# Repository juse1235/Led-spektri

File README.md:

# Led-spektri

Tuntuiko normaali haalarisalama liian yksinkertaiselta? Epäiletkö, että juotettavia LEDejä ei voi olla liikaa? Oletko aina haaveillut haalarimerkistä, jonka nähtyään kanssaopiskelijat pyörtyvät ihastuksesta?

Mikäli näin on, olet selvästikin motivoitunut nousemaan seuraavalle tasolle yöllisessä yökerhojen ja pystärien bling-bling-loisteessa. Tämä tanssilattioiden katseenvangitsija tarjoaa ainutkertaisen mahdollisuuden turruttaa itsensä vinoon juottuneille komponenteille ja v*tutukselle. Älä missaa tilaisuutta! Minä en missaisi.

Komponentit

| Tyyppi          |	Määrä  |	Huom                                                    |
| --------------- | ------ | -------------------------------------------------------- |
| Atmega328PB-AU  |1       |	Myös 328P voi toimia, mutta vaatii muutoksia kääntäjään |
| LED, 3 mm, jalallinen	|64 |	Ei värikoodia – käytä mielikuvitusta |
| Transistori, SOT-23|16 |	Käytössä MMBT4401, ei suurempaa väliä mallista, hyvä kuitenkin kestää vähintään 20 mA virtaa |
| Vastus, 0603 – 0805, 1+ kOhm | 16 |		Transistorien ohjaus |
| Etuvastus, 0805	|8	| Kirkkauden säätö, 100 – 500 ohmia lienee hyvä, säätää myös virrankulutusta, tekijällä käytössä 300 ohmia |
| Isohko vastus, noin 5 kOhm, 0603 |2	 | |
| Regulaattori, LP2985 – 3.3 |	1	| |
| Kondensaattori, 100 nF, 0805|	1	| |
| Kondensaattori, 10 uF, 0805|	1	| |
| Sulake, 500 mA, 1206	|1	| |
| Oskillaattori, 16 MHz |	1 |	Käytössä CSTCE16M0V53-R0 |
| MAX4466-mikrofonimoduuli |	1 |	Mikrofoneja löytyy eri herkkyyksillä, voi olla tuurissaan, mikä on käyttökelpoinen. Electret sinisellä piirilevyllä on toiminut toistaiseksi.|

## Yleinen toimintaperiaate
Ledien toimintaperiaate on samankaltainen kuin haalarisalamassakin, eli ledejä vilkutetaan matriisissa sarakkeittain säätämällä, mikä sarake saa yhteyden maahan ja suljettua virtapiirin. 

Mikrofoni kuuntelee ääntä, ja mikrokontrolleri lukee siitä tulevaa analogista signaalia jatkuvalla syötöllä. Näytepätkän ollessa valmis mikrokontrolleri tekee siitä fft-muunnoksen, joka voidaan esittää ledeillä.

Tähän merkkiin ei otettu edes mahdollisuudeksi käyttää 9 voltin paristolla, vaan käyttöjännite otetaan aina 5 voltin jännitelähteestä (lue: USB-kaapelin kautta varavirtalähteestä).

## Tarkempi piirikaavion analyysi
Piirikaavion olisi voinut päivittää paljon helpommin luettavaksi ja oikeille arvoille, jos Kicad 5.0 ei olisi niin epäyhteensopiva Kicad 4 -versioiden kanssa. 

Käyttöjännite tulee mikrokontrollerille ja 3,3 voltin regulaattorille sulakkeen kautta. Sulakkeen tehtävänä on luonnollisesti edes hieman suojata komponentteja oikosuluilta sun muilta lapsuksilta. Tässä otettiin mallia Arduinosta. Regulaattorin tarkoituksena on vain ja ainoastaan tuottaa tasaista käyttöjännitettä mikrofonimoduulille ja asettaa analoginen referenssitaso mikrokontrollerille mikrofonimoduulin analogisen signaalin lukua varten. 10 mikrofaradin kondensaattori C1 tasoittaa käyttöjännitteen pahimmat häiriöt, ja kondensaattori C_small (oikea arvo 100 nF) tekee saman 3,3 voltin linjalle.

Toisin kuin haalarisalamassa, tässä projektissa tarvitaan transistoreita rajoittamaan mikrokontrollerin kuormaa. Riittävän kirkkauden takaamiseksi ledin virraksi on hyvä määritellä noin 15 mA. Transistoreiksi päätyivät MMBT3904-transistorit, jotka perustuvat NPN-teknologiaan. Lähtökohtaisesti MOSFET-transistorienkin pitäisi toimia ihan yhtä hyvin, kunhan paketointi on sama. Transistorit vaativat vastukset kantavirran rajoittamiseksi (1 kOhmin vastukset piirikaaviossa ja jäljempänä esitetyssä piirilevyssä). Todennäköisesti arvoltaan suuremmatkin vastukset toimisivat aivan yhtä hyvin. 

##### HUOM!Projektia kokeiltiin toteuttaa myös puolella transistorimäärällä, mutta mikrokontrolleri ei kyennyt antamaan riittävästi virtaa yhden sarakkeen ledeille yhtä aikaa. Tämän korjaaminen vaatii joko todella herkkiä ja kirkkaita ledejä ja/tai koodimuutoksia, jolloin ainoastaan yksi led olisi samaan yhtä aikaa päällä (nyt maksimissaan kahdeksan).

Oskillaattori on geneerinen 16 megahertsin malli sisäänrakennetulla kuormakapasitanssilla, jollaisia näkee muun muassa Arduino Nanossa. Myös 20 megahertsin kidettä voi käyttää, mutta se vaatii muutoksia koodiin ja Atmegan… ööö, fuse… sulake ei liene oikea termi. Joka tapauksessa ”fuse”:ille pitää löytää oikeat asetukset.

Yksinkertaisuuden vuoksi mikrofonin kanssa päädyttiin vahvistimen sisältävään valmiiseen moduuliin. Moduuli tuottaa analogista signaalia, joka välitetään Atmegan ADC-pinniin, ja josta Atmega ottaa näytepätkän.

Kuten tarkimmat jo saattavat huomata, tekijä ei osannut tekovaiheessa tehdä ihmisystävällisiä kytkentöjä.

## Piirilevy
Tilanpuute oli valtava ongelma varsinaisen piirilevyn suunnittelun kanssa. Tästä syystä kaikkia komponentteja ei voitu sijoittaa levyn takapuolelle helpon korjattavuuden takaamiseksi, vaan osa komponenteista ja mikrofonimoduuli oli juotettava etupuolelle.

Yleinen ohje juottamiseen: juota ensin yksi komponentin nurkka kiinni niin, että komponentin muutkin juotoskohdat ovat paikallaan ja komponentti on oikeassa asennossa. Tämän jälkeen voi helposti juottaa loput paikat.

Juottaminen on hyvä aloittaa mikrokontrollerista. Tekijä juotti piirin reippaalla juoksutteella ja reippaalla tinankäytöllä, jolloin myös kontrollerin jalat olivat juottuneet yhteen. Tämän jälkeen ylimääräinen tina oli helppoa imeä tinaimunauhalla.

Muiden pintaliitoskomponenttien juottamisessa ei ole varsinaisesti mitään mainittavaa. U2 alemmassa kuvassa on 3,3 voltin regulaattori.
Kun pintaliitoskomponentit on juotettu, J7 ja J6 on yhdistettävä hyppylangalla. Miksi näin? Tilanpuutteen takia maatasoa ei ole muuten yhdistetty kontrollerin yläpuolelle ollenkaan. Onneksi tämä on matalan taajuuden sovellutus, joten tämmöiset temput ovat sallittuja...

Etupuolella on mainittava ledien juottamisesta sen verran, että pitkä jalka (anodi) menee ympyrän muotoiseen juotospisteeseen, ja lyhyt jalka (katodi) menee neliön muotoiseen juotospisteeseen. Kokemuksen jykevällä rintaäänellä voi sanoa, että juottakaa ledit myös mieluummin etupuolelle kuin takapuolelle. Mikrofonimoduulin ja piirilevyn väliin on suositeltavaa laittaa jotakin eristettä oikosulun välttämiseksi. Tantaalikondensaattorin viivalla merkitty pääty menee aina positiiviseen jännitteeseen kaiken järjen vastaisesti (etupuolen 10 mikrofaradin konkka). 

Levyn takapuoli

Levyn etupuoli

## Ohjelmointi
Ohjelmointi tapahtuu ISP-väylän kautta. ArduinoISP on tässä suositeltava ohjelmoija. Piirilevylle jätettiin ohjelmointipaikat myös UART-ohjelmointia varten, mutta niitä ei tässä tapauksessa tarvita ollenkaan. Tulevaisuuden generaatioista ne voikin poistaa tilaa säästääkseen.

##### Komennot Windowsille:

avrdude -C "C:\Program Files (x86)\Arduino\hardware\tools\avr\etc\avrdude.conf" -c avrisp -p m328pb -B3 -P COM7 -b 19200 -U flash:w:merkki.hex

avrdude -C "C:\Program Files (x86)\Arduino\hardware\tools\avr\etc\avrdude.conf" -c avrisp -p m328pb -B3 -P COM7 -b 19200 -U lfuse:w:0xff:m -U hfuse:w:0xde:m efuse:w:0x05:m

Jos avrdude.exe:ä ei ole asetettu Windowsin ympäristömuuttujiin, on edellä mainitut komennot ajettava ”Arduino\hardware\tools\avr\bin”-kansiosta. Polut ja oikea sarjaportti pitää toki tarkistaa tapauskohtaisesti.

##### Testaamattomat komennot Linuxille ja Macille:

avrdude -c avrisp -p m328pb -B3 -P /dev/ttyUSB0 -b 19200 -U flash:w:merkki.hex

avrdude -c avrisp -p m328pb -B3 -P /dev/ttyUSB0 -b 19200 -U lfuse:w:0xff:m -U hfuse:w:0xde:m efuse:w:0x05:m

Atmel Studio 7:llä tehty koodi ei ole mitään kauneinta katseltavaa, mutta joka tapauksessa se toimii. ChaN AVR FFT -kirjasto on otettu lievästi editoituna AVRFreaks-foorumilta ( https://www.avrfreaks.net/forum/64-point-fft-elm-chan-library), ja kirjasto löytyy myös erilaisina variaatioina eri puolilta internetiä. Alun perin koodi on oletettavasti julkaistu Elm-chanin kotisivulla (http://elm-chan.org/works/akilcd/report_e.html)

## Fyysinen rakenne
Kuumaliimaa kannattaa hyödyntää ainakin varsinaisen mikrofonielementin ja mikrofonimoduulipiirilevyn liitoskohdassa, sillä isku taittaa mikrofonin helposti. Lisäksi käyttöjännitetuloon on hyvä tehdä liimalla vedonpoisto.
Haalarimerkkiin integroimiseen ei ole suoria ohjeita, mutta on suositeltavaa tehdä painettuun merkkiin valmiit reiät. Mielikuvituksen ja insinööritaitojen käyttö on aiheellista, sillä ledien asentaminen merkin läpi haalarisalaman mukaisesti ei ole huollettavuuden takia järkevää.

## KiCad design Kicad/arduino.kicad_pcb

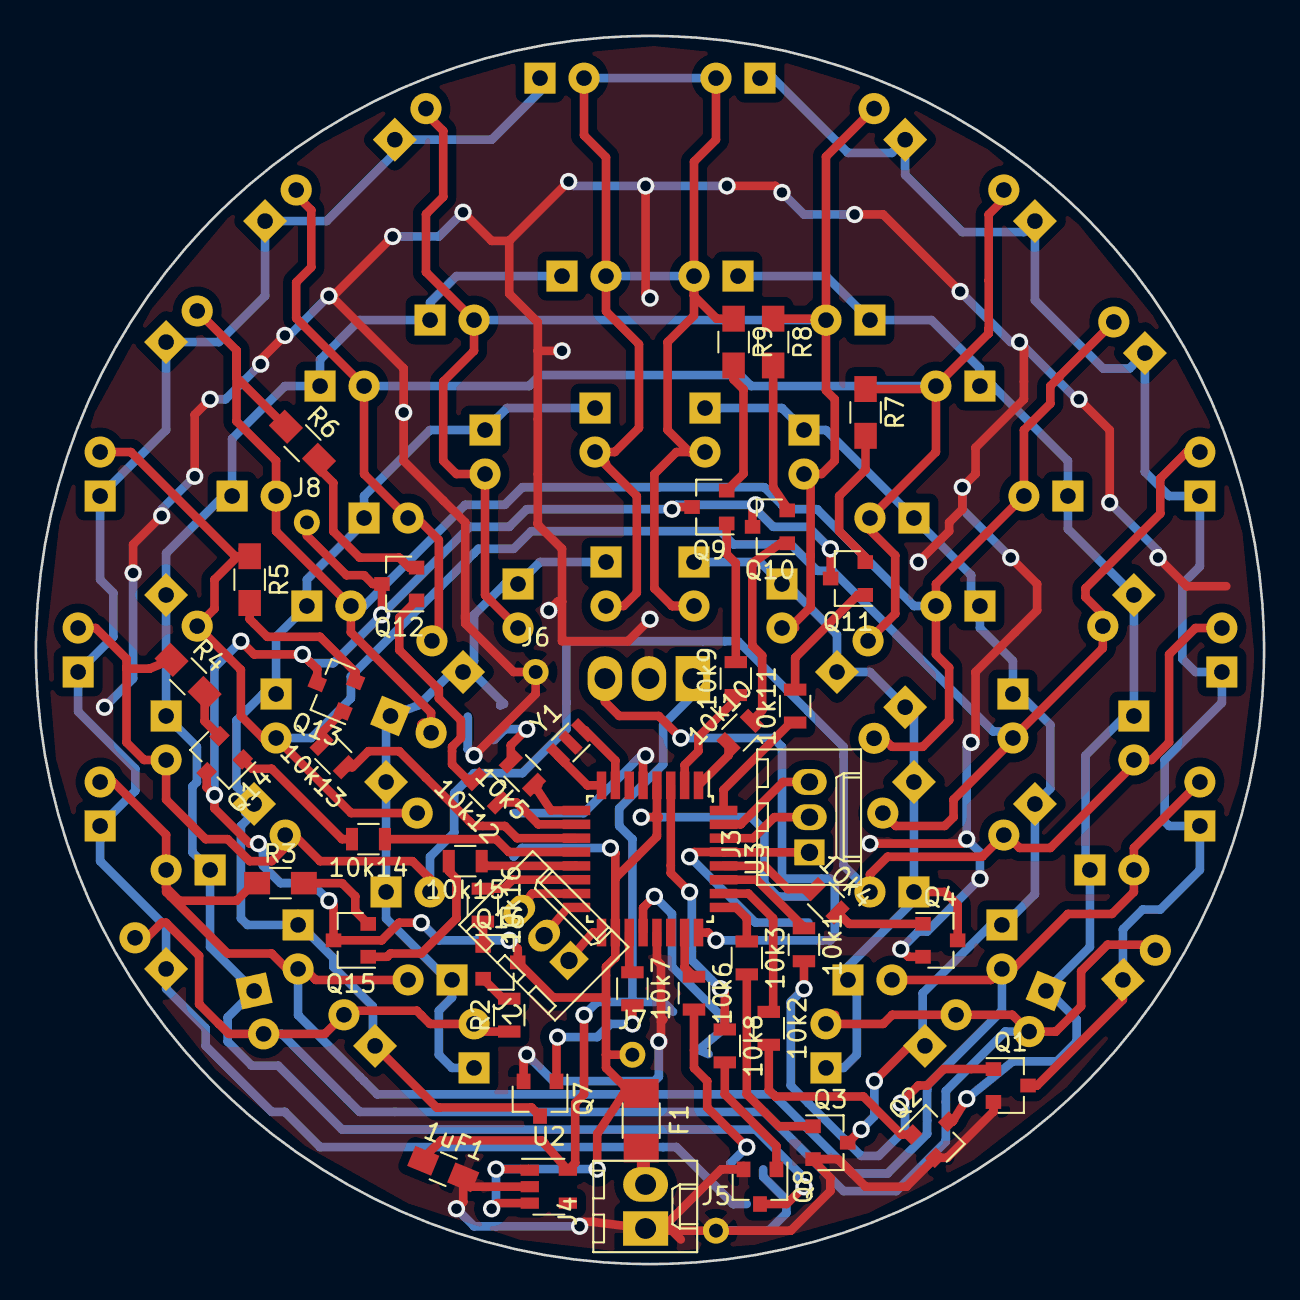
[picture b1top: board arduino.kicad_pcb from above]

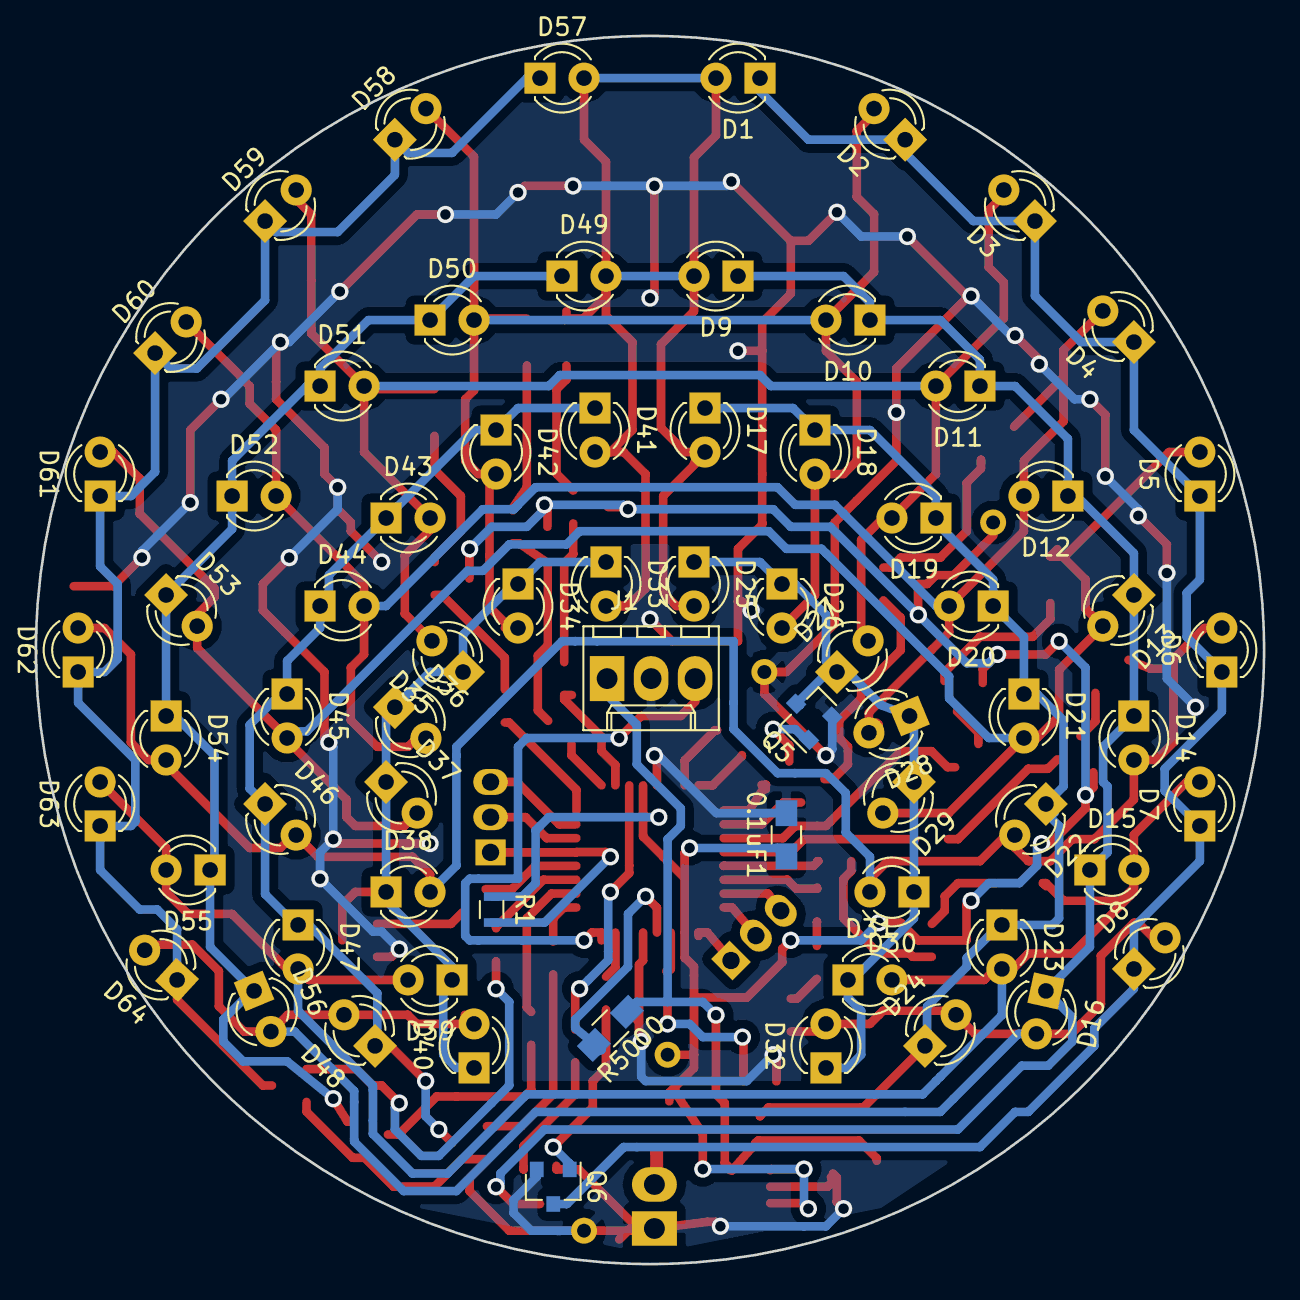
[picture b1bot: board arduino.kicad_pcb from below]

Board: 2 copper layers, 70.9 x 70.9 mm, 120 parts (70 on the bottom side), 70 nets.

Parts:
0.1uF1: C; C_0805_HandSoldering
1uF1: C_Small; C_0805_HandSoldering
10k1, 10k2, 10k3, 10k4, 10k5, 10k6, 10k7, 10k8, 10k9, 10k10, 10k11, 10k12, 10k13, 10k14, 10k15, 10k16: R; R_0805
D1, D2, D3, D4, D5, D6, D7, D8, D9, D10, D11, D12, D13, D14, D15, D16, D17, D18, D19, D20, D21, D22, D23, D24, D25, D26, D27, D28, D29, D30, D31, D32, D33, D34, D35, D36, D37, D38, D39, D40, D41, D42, D43, D44, D45, D46, D47, D48, D49, D50, D51, D52, D53, D54, D55, D56, D57, D58, D59, D60, D61, D62, D63, D64: IR204A; LED_D3.0mm
F1: 500mA; Fuse_SMD1206_Wave
J1: Conn_01x03; Molex_KK-6410-03_03x2.54mm_Straight
J2, J3: Conn_01x03; kolmijalka
J4: Conn_01x02; Molex_KK-6410-02_02x2.54mm_Straight
J5, J6, J7, J8: Conn_01x01; Measurement_Point_Round-TH_Small
Q1, Q2, Q3, Q4, Q5, Q6, Q7, Q8, Q9, Q10, Q11, Q12, Q13, Q14, Q15, Q16: MMBT3904; SOT-23
R1: 10kohm; L_0603
R2: R; R_0805
R3, R4, R5, R6, R7, R8, R9: R; R_0805_HandSoldering
R5000: 5K; R_0805_HandSoldering
U2: LP2985-3.3; SOT-23-5
U3: ATMEGA328PB-AU; TQFP-32_7x7mm_Pitch0.8mm
Y1: Resonator; resonator

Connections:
+5V: F1.2, J4.2
GND: 0.1uF1.2, 1uF1.2, J1.2, J4.1, J5.1, J6.1, Q1.2, Q2.2, Q3.2, Q4.2, Q5.2, Q6.2, Q7.2, Q8.2, U2.2, U3.5, U3.21, Y1.2
unnamed: 0.1uF1.1, F1.1, J7.1, J8.1, Q9.3, Q10.3, Q11.3, Q12.3, Q13.3, Q14.3, Q15.3, Q16.3, R1.1, U2.1, U2.3, U3.4, U3.18
unnamed: 1uF1.1, J1.1, R5000.1, U2.5
unnamed: 10k1.1, U3.27
unnamed: 10k1.2, Q1.1
unnamed: 10k2.1, U3.26
unnamed: 10k2.2, Q2.1
unnamed: 10k3.1, U3.25
unnamed: 10k3.2, Q3.1
unnamed: 10k4.1, U3.28
unnamed: 10k4.2, Q4.1
unnamed: 10k5.1, U3.9
unnamed: 10k5.2, Q5.1
unnamed: 10k6.1, U3.23
unnamed: 10k6.2, Q6.1
unnamed: 10k7.1, U3.19
unnamed: 10k7.2, Q7.1
unnamed: 10k8.1, U3.3
unnamed: 10k8.2, Q8.1
unnamed: 10k9.1, U3.2
unnamed: 10k9.2, Q9.1
unnamed: 10k10.1, U3.1
unnamed: 10k10.2, Q10.1
unnamed: 10k11.1, U3.32
unnamed: 10k11.2, Q11.1
unnamed: 10k12.1, U3.10
unnamed: 10k12.2, Q12.1
unnamed: 10k13.1, U3.11
unnamed: 10k13.2, Q13.1
unnamed: 10k14.1, U3.12
unnamed: 10k14.2, Q14.1
unnamed: 10k15.1, U3.13
unnamed: 10k15.2, Q15.1
unnamed: 10k16.1, U3.14
unnamed: 10k16.2, Q16.1
unnamed: D1.1, D2.1, D3.1, D4.1, D5.1, D6.1, D7.1, D8.1, Q6.3
unnamed: D1.2, D9.2, D17.2, D25.2, D33.2, D41.2, D49.2, D57.2, R9.1
unnamed: D9.1, D10.1, D11.1, D12.1, D13.1, D14.1, D15.1, D16.1, Q8.3
unnamed: D2.2, D10.2, D18.2, D26.2, D34.2, D42.2, D50.2, D58.2, R8.1
unnamed: D3.2, D11.2, D19.2, D27.2, D35.2, D43.2, D51.2, D59.2, R7.1
unnamed: D4.2, D12.2, D20.2, D28.2, D36.2, D44.2, D52.2, D60.2, R6.1
unnamed: D5.2, D13.2, D21.2, D29.2, D37.2, D45.2, D53.2, D61.2, R5.1
unnamed: D6.2, D14.2, D22.2, D30.2, D38.2, D46.2, D54.2, D62.2, R4.1
unnamed: D7.2, D15.2, D23.2, D31.2, D39.2, D47.2, D55.2, D63.2, R3.1
unnamed: D8.2, D16.2, D24.2, D32.2, D40.2, D48.2, D56.2, D64.2, R2.1
unnamed: D17.1, D18.1, D19.1, D20.1, D21.1, D22.1, D23.1, D24.1, Q7.3
unnamed: D25.1, D26.1, D27.1, D28.1, D29.1, D30.1, D31.1, D32.1, Q5.3
unnamed: D33.1, D34.1, D35.1, D36.1, D37.1, D38.1, D39.1, D40.1, Q4.3
unnamed: D41.1, D42.1, D43.1, D44.1, D45.1, D46.1, D47.1, D48.1, Q3.3
unnamed: D49.1, D50.1, D51.1, D52.1, D53.1, D54.1, D55.1, D56.1, Q2.3
unnamed: D57.1, D58.1, D59.1, D60.1, D61.1, D62.1, D63.1, D64.1, Q1.3
unnamed: J1.3, U3.24
unnamed: J2.1, U3.17
unnamed: J2.2, U3.16
unnamed: J2.3, U3.15
unnamed: J3.1, R1.2, U3.29
unnamed: J3.2, U3.30
unnamed: J3.3, U3.31
unnamed: Q9.2, R9.2
unnamed: Q10.2, R8.2
unnamed: Q11.2, R7.2
unnamed: Q12.2, R6.2
unnamed: Q13.2, R5.2
unnamed: Q14.2, R4.2
unnamed: Q15.2, R3.2
unnamed: Q16.2, R2.2
unnamed: R5000.2, U3.20
unnamed: U3.7, Y1.3
unnamed: U3.8, Y1.1
